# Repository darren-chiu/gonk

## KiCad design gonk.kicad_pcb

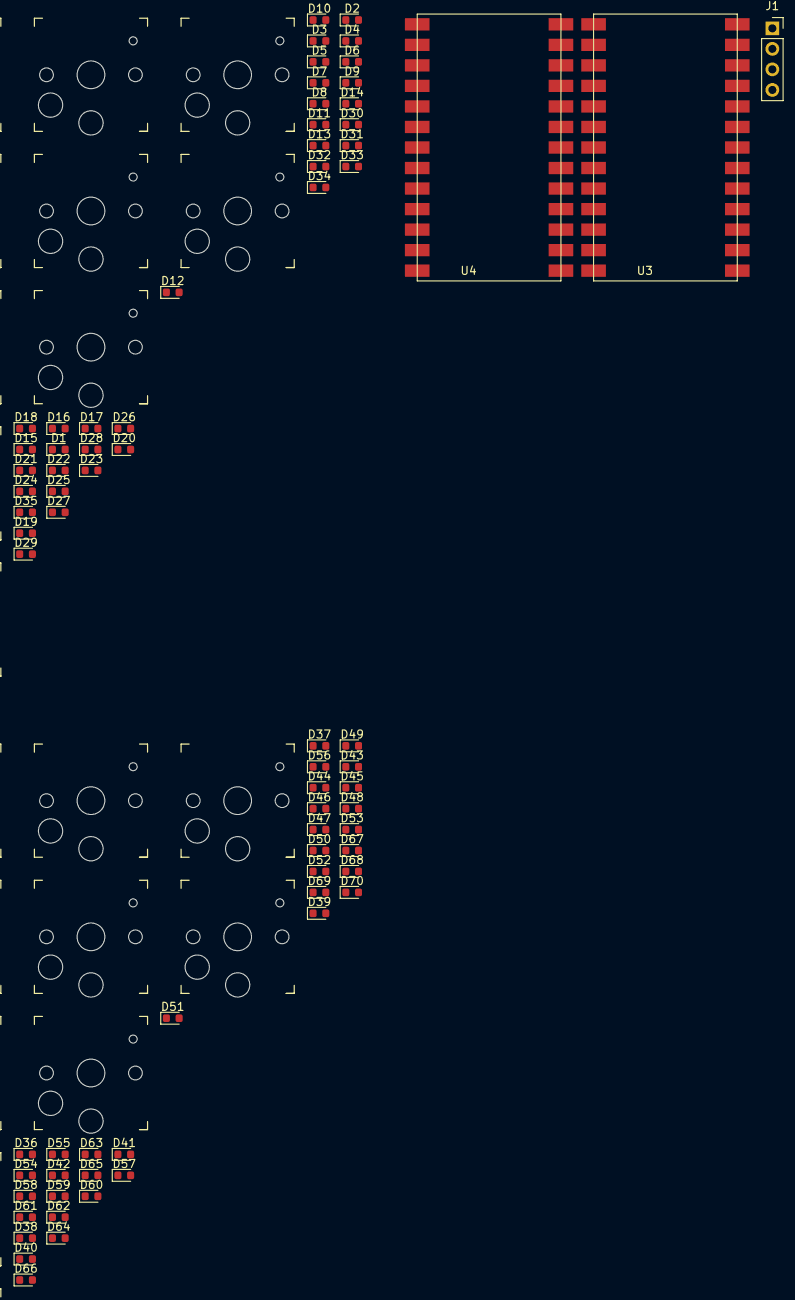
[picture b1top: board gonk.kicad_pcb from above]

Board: 2 copper layers, 143 parts (0 on the bottom side), 98 nets, no tracks yet.

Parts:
D1, D2, D3, D4, D5, D6, D7, D8, D9, D10, D11, D12, D13, D14, D15, D16, D17, D18, D19, D20, D21, D22, D23, D24, D25, D26, D27, D28, D29, D30, D31, D32, D33, D34, D35, D36, D37, D38, D39, D40, D41, D42, D43, D44, D45, D46, D47, D48, D49, D50, D51, D52, D53, D54, D55, D56, D57, D58, D59, D60, D61, D62, D63, D64, D65, D66, D67, D68, D69, D70: D; D_0603_1608Metric
J1: Conn_01x04_Female; PinSocket_1x04_P2.54mm_Vertical
K1, K2, K3, K4, K5, K6, K7, K8, K9, K10, K11, K12, K13, K14, K15, K16, K17, K18, K19, K20, K21, K22, K23, K24, K25, K26, K27, K28, K29, K30, K31, K32, K33, K34, K35, K36, K37, K38, K39, K40, K41, K42, K43, K44, K45, K46, K47, K48, K49, K50, K51, K52, K53, K54, K55, K56, K57, K58, K59, K60, K61, K62, K63, K64, K65, K66, K67, K68, K69, K70: KEYSW; Kailh_socket_PG1350
U3, U4: kb2040

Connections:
/RAW: J1.2, U4.15
/SCL: J1.3, U3.7
/SDA: J1.4, U3.6
/col0_L: K1.1, K2.1, K3.1, K4.1, K29.1, U4.9
/col0_R: K36.1, K37.1, K38.1, K39.1, K40.1, U3.9
/col1_L: K5.1, K6.1, K7.1, K8.1, K30.1, U4.10
/col1_R: K41.1, K42.1, K43.1, K44.1, K45.1, U3.10
/col2_L: K9.1, K10.1, K11.1, K12.1, K31.1, U4.11
/col2_R: K46.1, K47.1, K48.1, K49.1, K50.1, U3.11
/col3_L: K13.1, K14.1, K15.1, K16.1, K32.1, U4.12
/col3_R: K51.1, K52.1, K53.1, K54.1, K55.1, U3.12
/col4_L: K17.1, K18.1, K19.1, K20.1, K33.1, U4.13
/col4_R: K56.1, K57.1, K58.1, K59.1, K60.1, U3.13
/col5_L: K24.1, K34.1, U4.19
/col5_R: K64.1, K65.1, U3.19
/col6_L: K25.1, K26.1, K27.1, K28.1, K35.1, U4.20
/col6_R: K66.1, K67.1, K68.1, K69.1, K70.1, U3.20
/row0_L: D1.1, D5.1, D9.1, D13.1, D17.1, D21.1, D25.1, U4.2
/row0_R: D36.1, D41.1, D46.1, D51.1, D56.1, D61.1, D66.1, U3.2
/row1_L: D2.1, D6.1, D10.1, D14.1, D18.1, D22.1, D26.1, U4.3
/row1_R: D37.1, D42.1, D47.1, D52.1, D57.1, D62.1, D67.1, U3.3
/row2_L: D3.1, D7.1, D11.1, D15.1, D19.1, D23.1, D27.1, U4.6
/row2_R: D38.1, D43.1, D48.1, D53.1, D58.1, D63.1, D68.1, U3.21
/row3_L: D4.1, D8.1, D12.1, D16.1, D20.1, D24.1, D28.1, U4.7
/row3_R: D39.1, D44.1, D49.1, D54.1, D59.1, D64.1, D69.1, U3.22
/row4_L: D29.1, D30.1, D31.1, D32.1, D33.1, D34.1, D35.1, U4.8
/row4_R: D40.1, D45.1, D50.1, D55.1, D60.1, D65.1, D70.1, U3.8
GND: J1.1, U4.16
unnamed: D1.2, K1.2
unnamed: D2.2, K2.2
unnamed: D3.2, K3.2
unnamed: D4.2, K4.2
unnamed: D5.2, K5.2
unnamed: D6.2, K6.2
unnamed: D7.2, K7.2
unnamed: D8.2, K8.2
unnamed: D9.2, K9.2
unnamed: D10.2, K10.2
unnamed: D11.2, K11.2
unnamed: D12.2, K12.2
unnamed: D13.2, K13.2
unnamed: D14.2, K14.2
unnamed: D15.2, K15.2
unnamed: D16.2, K16.2
unnamed: D17.2, K17.2
unnamed: D18.2, K18.2
unnamed: D19.2, K19.2
unnamed: D20.2, K20.2
unnamed: D21.2, K21.2
unnamed: D22.2, K22.2
unnamed: D23.2, K23.2
unnamed: D24.2, K24.2
unnamed: D25.2, K25.2
unnamed: D26.2, K26.2
unnamed: D27.2, K27.2
unnamed: D28.2, K28.2
unnamed: D29.2, K29.2
unnamed: D30.2, K30.2
unnamed: D31.2, K31.2
unnamed: D32.2, K32.2
unnamed: D33.2, K33.2
unnamed: D34.2, K34.2
unnamed: D35.2, K35.2
unnamed: D36.2, K36.2
unnamed: D37.2, K37.2
unnamed: D38.2, K38.2
unnamed: D39.2, K39.2
unnamed: D40.2, K40.2
unnamed: D41.2, K41.2
unnamed: D42.2, K42.2
unnamed: D43.2, K43.2
unnamed: D44.2, K44.2
unnamed: D45.2, K45.2
unnamed: D46.2, K46.2
unnamed: D47.2, K47.2
unnamed: D48.2, K48.2
unnamed: D49.2, K49.2
unnamed: D50.2, K50.2
unnamed: D51.2, K51.2
unnamed: D52.2, K52.2
unnamed: D53.2, K53.2
unnamed: D54.2, K54.2
unnamed: D55.2, K55.2
unnamed: D56.2, K56.2
unnamed: D57.2, K57.2
unnamed: D58.2, K58.2
unnamed: D59.2, K59.2
unnamed: D60.2, K60.2
unnamed: D61.2, K61.2
unnamed: D62.2, K62.2
unnamed: D63.2, K63.2
unnamed: D64.2, K64.2
unnamed: D65.2, K65.2
unnamed: D66.2, K66.2
unnamed: D67.2, K67.2
unnamed: D68.2, K68.2
unnamed: D69.2, K69.2
unnamed: D70.2, K70.2

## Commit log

2022-01-01 3D render checked
2022-01-01 Add Trrs connector next
2022-03-11 using esp32 now
2022-03-11 Added heiarchical
